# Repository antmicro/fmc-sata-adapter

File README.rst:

===================
FMC to SATA Adapter
===================

Copyright (c) 2021 `Antmicro <https://www.antmicro.com>`_

.. image:: Images/fmc2sata.jpg
   :scale: 40%

Overview
========

This repository includes PCB design files for an experimental expansion board that lets you connect SATA III SSD devices over an M.2 slot to FMC mezzanine connectors available on many FPGA development platforms including Digilent `Nexys Video Artix-7 Board <https://store.digilentinc.com/nexys-video-artix-7-fpga-trainer-board-for-multimedia-applications/>`_.

License
=======

`Apache-2.0 <LICENSE>`_

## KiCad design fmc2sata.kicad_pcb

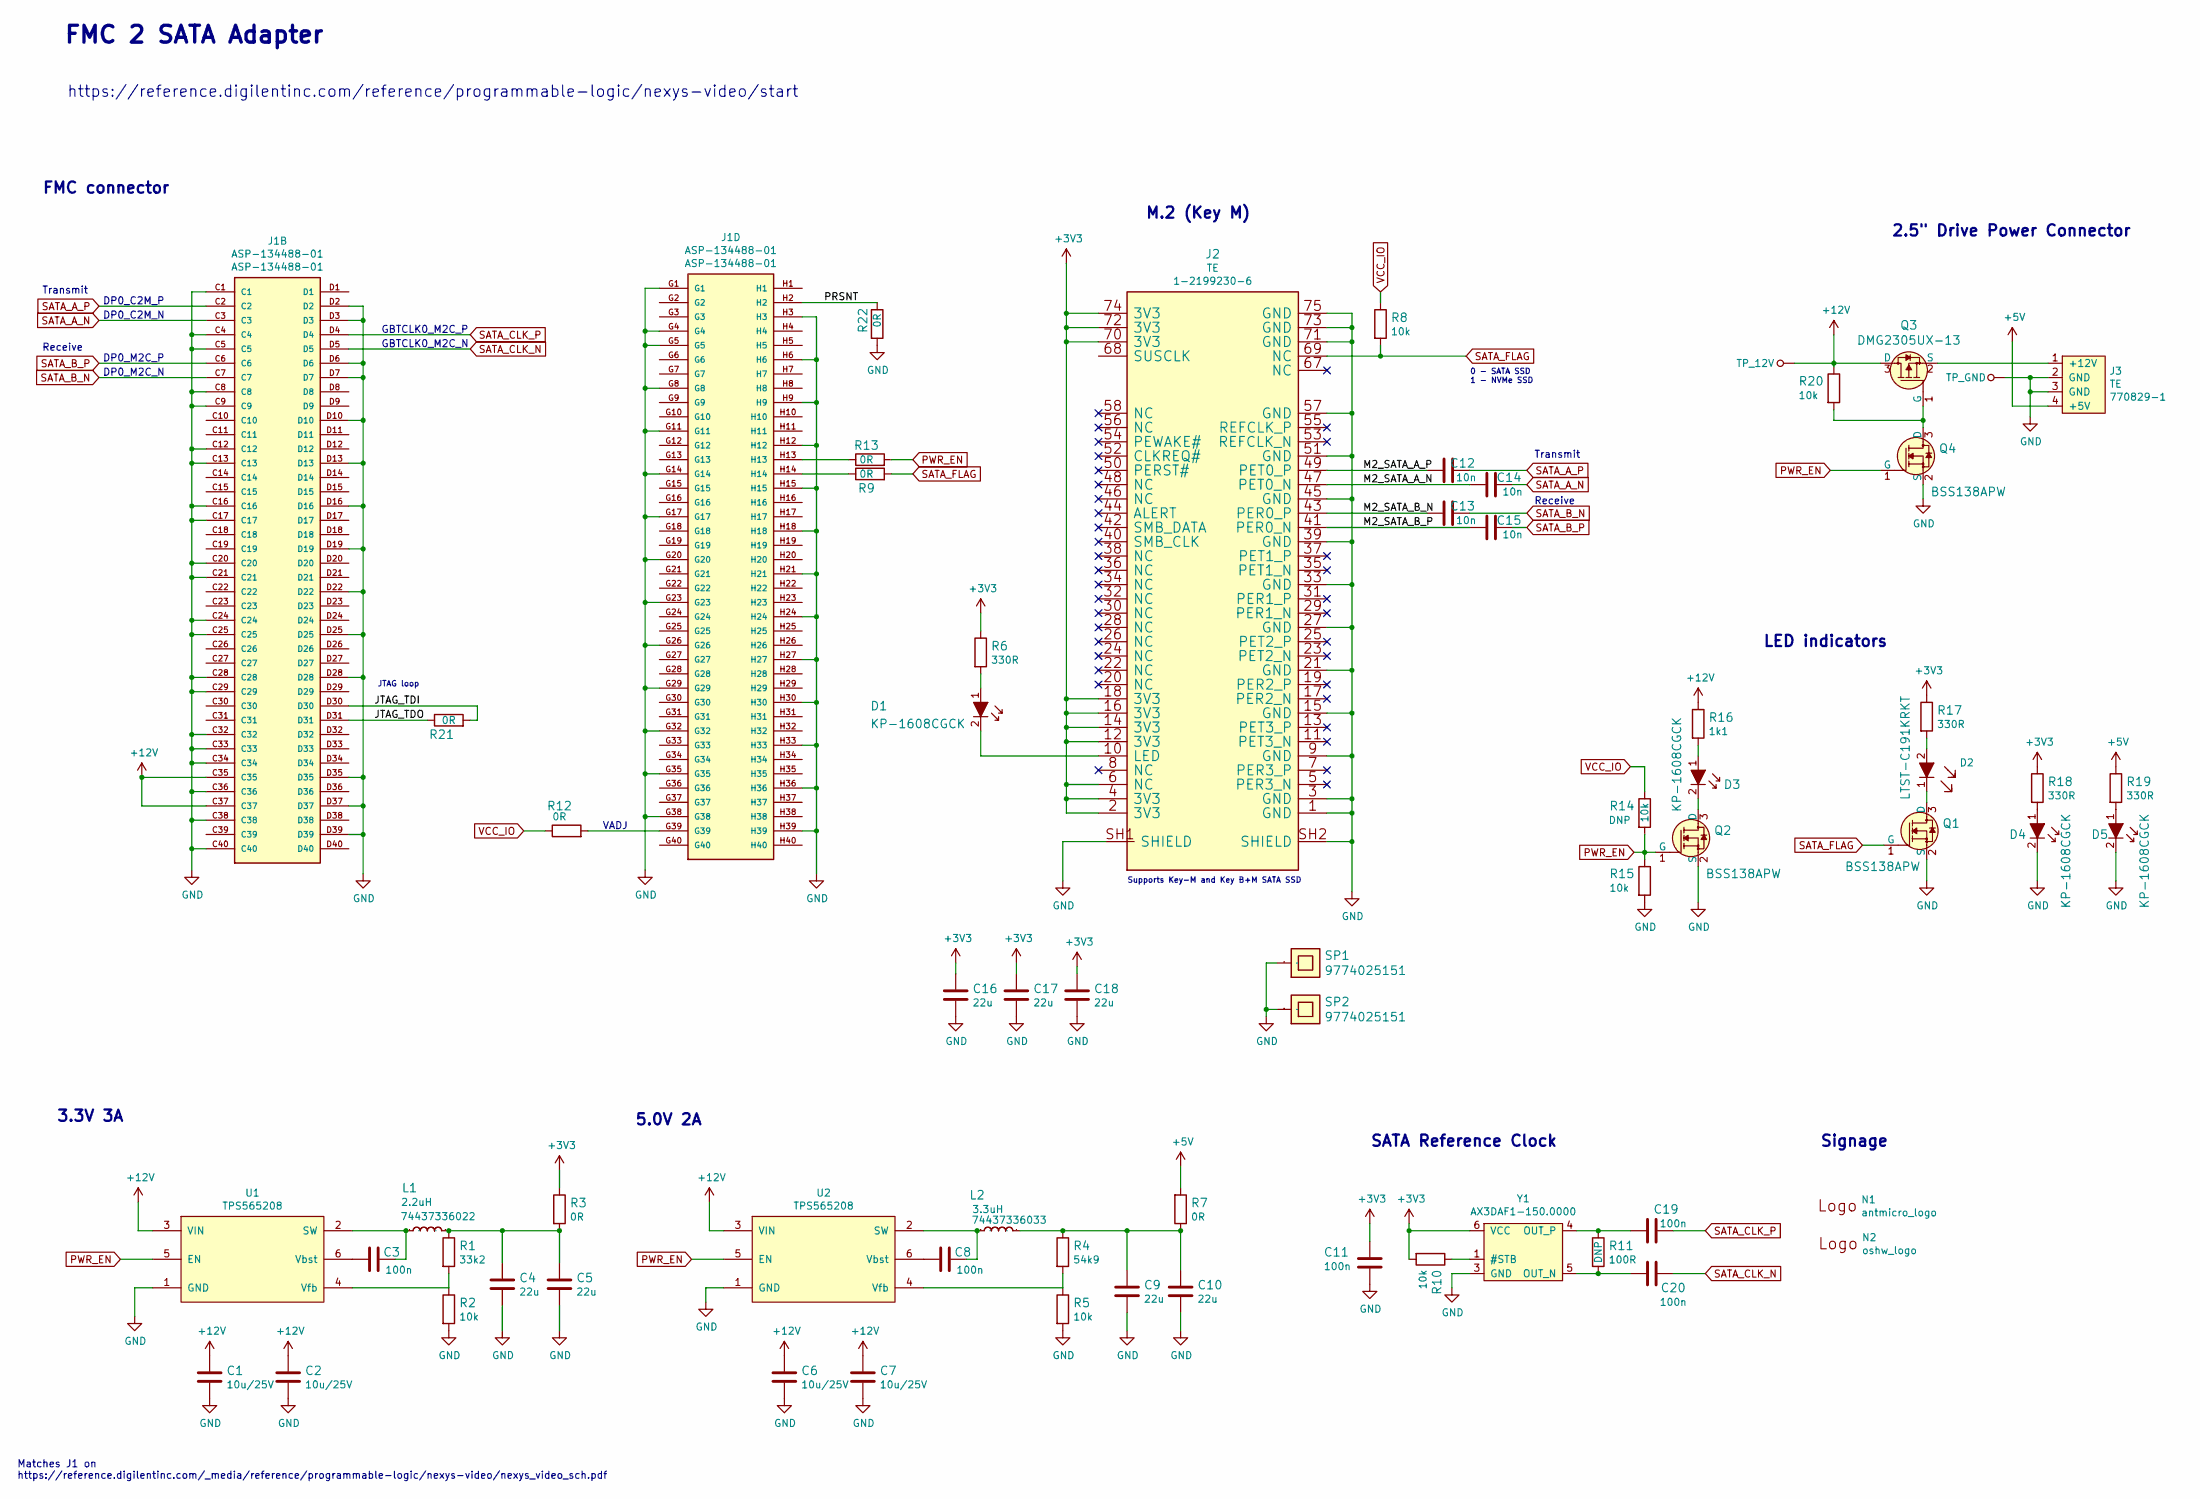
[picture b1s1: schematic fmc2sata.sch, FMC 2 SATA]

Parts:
C1, C2, C6, C7: C_10u_25V_0603; 0603-cap; MPN C1608X5R1E106M080AC
C3, C8: C_100n_0603; 0603-cap; MPN 0603YC104KAZ2A
C4, C5, C9, C10, C16, C17, C18: C_22u_0805_10V; 0805-cap; MPN 0805ZD226MAT2A
C11, C19, C20: C_100n_0402; 0402-cap; MPN 0402X104K6R3CT
C12, C13, C14, C15: C_10n_0402; 0402-cap; MPN 04025G103ZAT2A
D1, D3, D4, D5: KP-1608CGCK; LED_0603; MPN KP-1608CGCK
D2: LTST-C191KRKT; LED_0603; MPN LTST-C191KRKT
J1: ASP-134488-01; MPN ASP-134488-01
J2: 1-2199230-6; MPN 1-2199230-6
J3: te-770829-1; MPN 770829-1
L1: WE_74437336022; MPN 74437336022
L2: WE_74437336033; MPN 74437336033
N1: antmicro_logo; antmicro-logo_scaled_20mm
N2: oshw_logo; oshw-logo
Q1, Q2, Q4: BSS138APW; SC70-3; MPN BSS138PW
Q3: DMG2305UX-13; SOT-23-3; MPN DMG2305UX-13
R1: R_33k2_0402; 0402-res; MPN ERJ2RKF3322X
R2, R5, R8, R10, R14, R15, R20: R_10k_0402; 0402-res; MPN CRCW040210K0FKEDHP
R3, R7, R9, R12, R13, R21, R22: R_0R_0402; 0402-res; MPN ERJ2GE0R00X
R4: R_54k9_0402; 0402-res; MPN MCMR04X5492FTL
R6, R17, R18, R19: R_330R_0402; 0402-res; MPN MCMR04X3300FTL
R11: R_100R_0402; 0402-res; MPN CR0402-FX-1000GLF
R16: R_1k1_0402; 0402-res; MPN ERJ2RKF1101X
SP1, SP2: 9774025151; MPN 9774025151
TP_12V: TP_SMD1MM; Testpoint_smd_1mm
TP_GND: TP_SMD1MM; Testpoint_smd_1mm
U1, U2: TPS565208; SOT-23-6; MPN TPS565208DDCT
Y1: AX3DAF1-150.0000; AX3DAF1; MPN ASFLMB-12.000MHZ-LC-T

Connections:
+3V3: C11.1, C16.1, C17.1, C18.1, J2.2 (3V3), J2.4 (3V3), J2.6 (NC), J2.12 (3V3), J2.14 (3V3), J2.16 (3V3), J2.18 (3V3), J2.70 (3V3), J2.72 (3V3), J2.74 (3V3), R3.1, R6.1, R10.2, R17.1, R18.1, Y1.6 (VCC)
+5V: J3.4 (+5V), R7.2, R19.1
+12V: C1.1, C2.1, C6.1, C7.1, J1.C35, J1.C37, Q3.3 (D), R16.1, R20.1, TP_12V.1, U1.3 (VIN), U2.3 (VIN); also elsewhere on the board
/JTAG_TDI: J1.D30, R21.2
/JTAG_TDO: J1.D31, R21.1
/M2_SATA_A_N: C14.2, J2.47 (PET0_N)
/M2_SATA_A_P: C12.2, J2.49 (PET0_P)
/M2_SATA_B_N: C13.2, J2.43 (PER0_P)
/M2_SATA_B_P: C15.2, J2.41 (PER0_N)
/PRSNT: J1.H2, R22.1
GND: C1.2, C2.2, C4.2, C5.2, C6.2, C7.2, C9.2, C10.2, C11.2, C16.2, C17.2, C18.2, D4.2, D5.2, J1.C1, J1.C4, J1.C5, J1.C8, J1.C9, J1.C12, J1.C13, J1.C16, J1.C17, J1.C20, J1.C21, J1.C24, J1.C25, J1.C28, J1.C29, J1.C32, J1.C33, J1.C34, J1.C36, J1.C38, J1.C40, J1.D2, J1.D3, J1.D6, J1.D7, J1.D10, J1.D13, J1.D16, J1.D19, J1.D22, J1.D25, J1.D28, J1.D35, J1.D37, J1.D39, J1.G1, J1.G4, J1.G5, J1.G8, J1.G11, J1.G14, J1.G17, J1.G20, J1.G23, J1.G26, J1.G29, J1.G32, J1.G35, J1.G38, J1.H3, J1.H6, J1.H9, J1.H12, J1.H15, J1.H18, J1.H21, J1.H24, J1.H27, J1.H30, J1.H33, J1.H36, J1.H39, J2.1 (GND), J2.3 (GND), J2.9 (GND), J2.15 (GND), J2.21 (GND), J2.27 (GND), J2.33 (GND), J2.39 (GND), J2.45 (GND), J2.51 (GND), J2.57 (GND), J2.71 (GND), J2.73 (GND), J2.75 (GND), J2.SH1 (SHIELD), J2.SH2 (SHIELD), J3.2 (GND), J3.3 (GND), Q1.2 (S), Q2.2 (S), Q4.2 (S), R2.2, R5.2, R15.2, R22.2, SP1.1, SP2.1, TP_GND.1, U1.1 (GND), U2.1 (GND), Y1.3 (GND); also elsewhere on the board
unnamed: C3.1, L1.1, U1.2 (SW)
unnamed: C3.2, U1.6 (Vbst)
unnamed: C4.1, C5.1, L1.2, R1.1, R3.2
unnamed: C8.1, L2.1, U2.2 (SW)
unnamed: C8.2, U2.6 (Vbst)
unnamed: C9.1, C10.1, L2.2, R4.1, R7.1
unnamed: C19.2, R11.1, Y1.4 (OUT_P)
unnamed: C20.2, R11.2, Y1.5 (OUT_N)
unnamed: D1.1, R6.2
unnamed: D1.2, J2.10 (LED)
unnamed: D2.1, Q1.3 (D)
unnamed: D2.2, R17.2
unnamed: D3.1, R16.2
unnamed: D3.2, Q2.3 (D)
unnamed: D4.1, R18.2
unnamed: D5.1, R19.2
unnamed: J1.G39, R12.2
unnamed: J1.H13, R13.1
unnamed: J1.H14, R9.1
unnamed: J3.1 (+12V), Q3.2 (S)
unnamed: Q3.1 (G), Q4.3 (D), R20.2
unnamed: R1.2, R2.1, U1.4 (Vfb)
unnamed: R4.2, R5.1, U2.4 (Vfb)
unnamed: R10.1, Y1.1 (#STB)
PWR_EN: Q2.1 (G), Q4.1 (G), R13.2, R14.2, R15.1, U1.5 (EN), U2.5 (EN)
SATA_A_N: C14.1, J1.C3
SATA_A_P: C12.1, J1.C2
SATA_B_N: C13.1, J1.C7
SATA_B_P: C15.1, J1.C6
SATA_CLK_N: C20.1, J1.D5
SATA_CLK_P: C19.1, J1.D4
SATA_FLAG: J2.69 (NC), Q1.1 (G), R8.2, R9.2
VCC_IO: R8.1, R12.1, R14.1

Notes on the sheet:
FMC 2 SATA Adapter
https://reference.digilentinc.com/reference/programmable-logic/nexys-video/start
0 - SATA SSD 1 - NVMe SSD
Supports Key-M and Key B+M SATA SSD
FMC connector
M.2 (Key M)
Matches J1 on https://reference.digilentinc.com/_media/reference/programmable-logic/nexys-video/nexys_video_sch.pdf
3.3V 3A
SATA Reference Clock
5.0V 2A
GBTCLK0_M2C_P
GBTCLK0_M2C_N
DP0_C2M_P
DP0_C2M_N
DP0_M2C_P
DP0_M2C_N
Transmit
Receive
2.5" Drive Power Connector
Signage
VADJ
LED indicators
JTAG loop

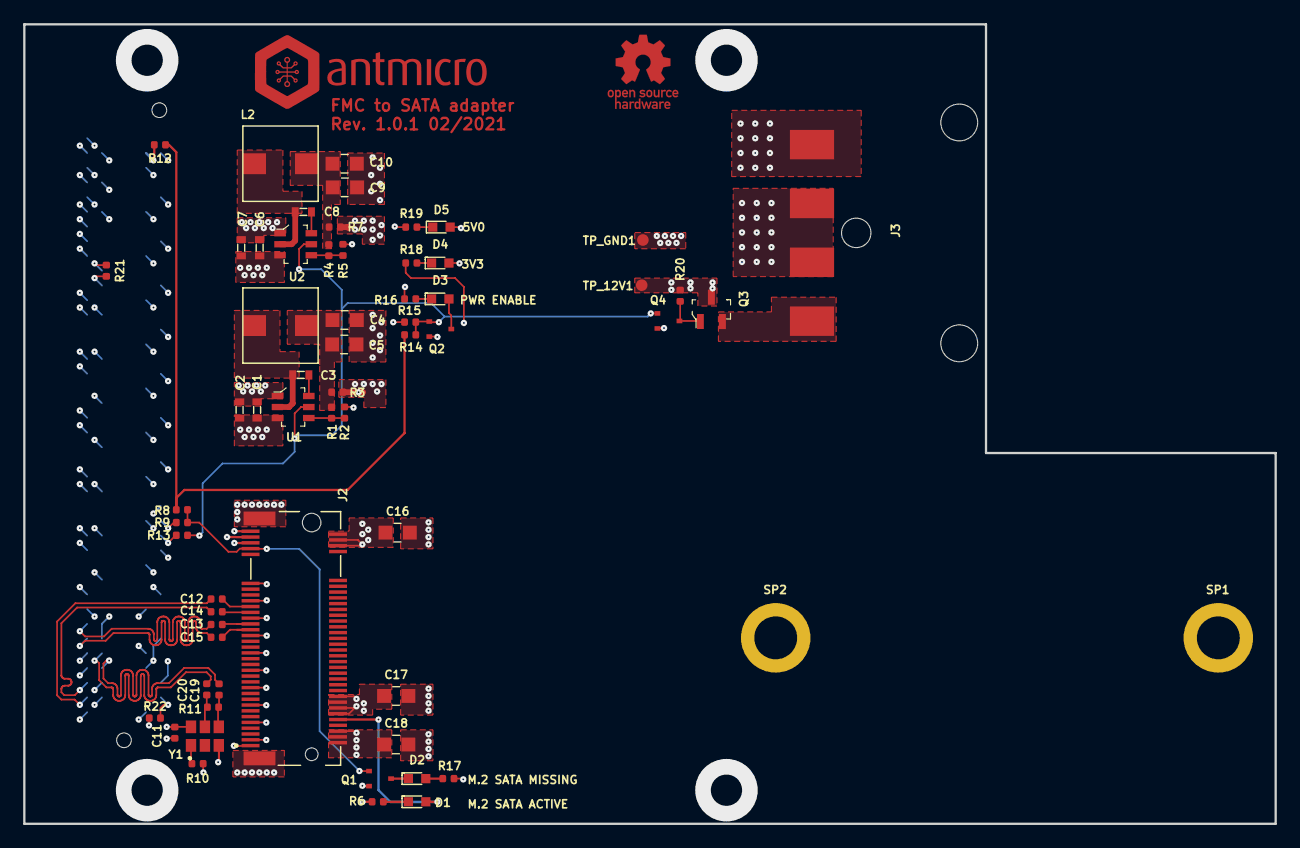
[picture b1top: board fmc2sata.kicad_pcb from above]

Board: 4 copper layers, 108.0 x 69.0 mm, 65 parts (1 on the bottom side), 44 nets.

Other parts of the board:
TP_12V1: TP_SMD1MM; Testpoint_smd_1mm
TP_GND1: TP_SMD1MM; Testpoint_smd_1mm

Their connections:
+12V: TP_12V1.1; also elsewhere on the board
GND: TP_GND1.1; also elsewhere on the board

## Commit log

2021-01-18 Add README
2021-01-18 Add initial project file
2021-01-18 Update folder structure
2021-01-18 Add FMC male connector
2021-01-25 Add .gitignore
2021-01-25 Connect SATA lanes
2021-01-25 Add second M.2 mouting stud
2021-01-25 Add M.2 with basic connections
2021-01-25 Add board fastening holes
2021-01-25 Add DC/DC converters
2021-01-25 Add basic PCB outline
2021-01-25 Include FMC fastening holes
2021-01-25 Add LICENSE
2021-01-25 Cleanup
2021-01-25 Add initial component placement
2021-01-25 Add 2.5" SATA connector and 150MHz LVDS REF CLK generator
2021-01-25 Add AMP power connector
2021-01-25 Add power planes
2021-01-25 Component cleanup
2021-01-25 Add board name
2021-01-25 Update compoent placement
2021-01-25 Layout in progress
2021-01-25 Add PWR indicators
2021-01-25 Routing in progress
2021-01-25 Add filtering caps
2021-01-25 Update designators, DRC clean
2021-01-25 Add length tunning
2021-01-25 Update local libraries
2021-01-25 Update 3D Vis
2021-01-25 All signals connected, DRC clean
2021-01-25 Add 3DVis
2021-01-25 README: fix link
2021-01-26 README: update link
2021-02-09 Bump release to 1.0.1
2021-02-09 Remove C39 connection
2021-02-09 Add capacitive coupling to Y1
2021-02-09 Update layout, DRC clean
2021-02-09 Add testpads for power supply - DRC clean
2021-02-09 Minor fix in README
2021-02-09 Bump release month on PCB
2021-02-09 Minor fixes in sch
2021-03-03 Add photo
2021-04-29 README: update design status
2021-10-15 Minor review of README
2021-10-15 Even more minor review of README
2023-08-07 Notes added by 'git notes add'
